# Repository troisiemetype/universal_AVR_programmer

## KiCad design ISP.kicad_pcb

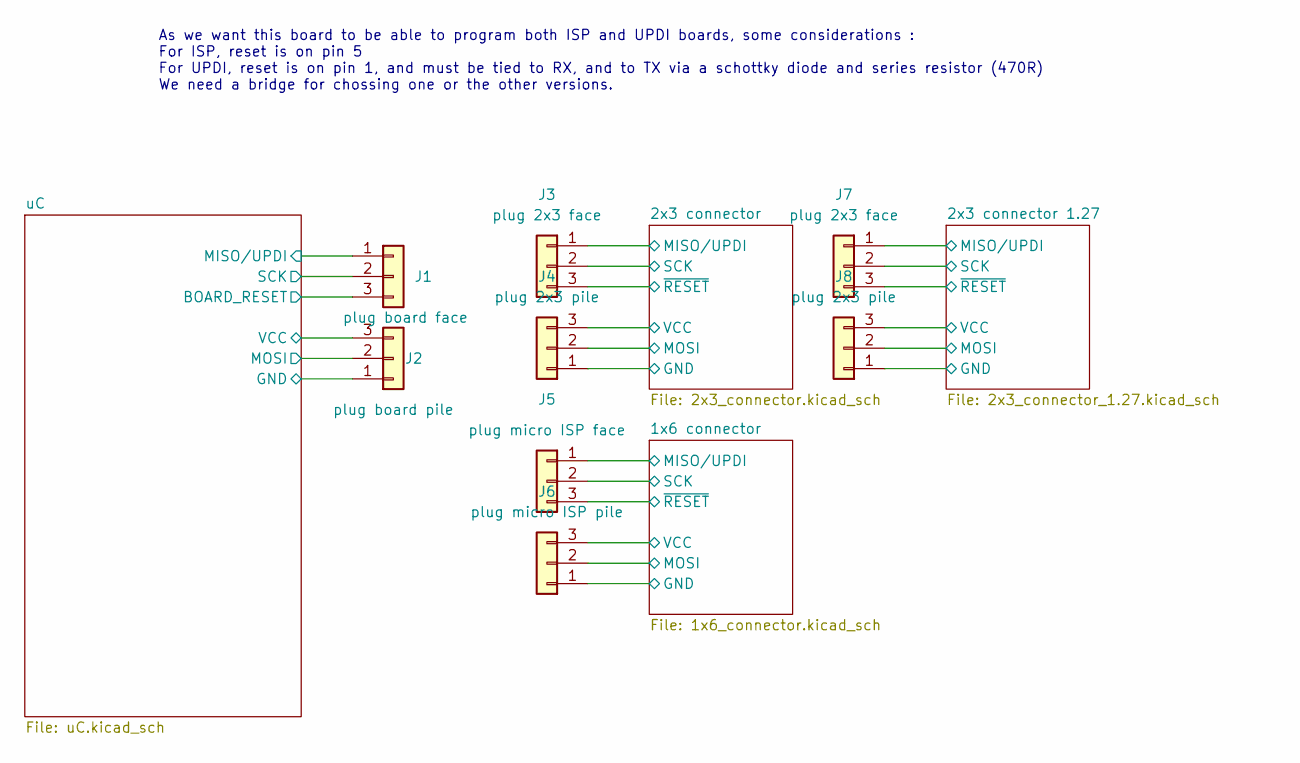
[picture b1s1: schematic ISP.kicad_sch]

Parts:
J1: plug board face; Connector_pad_1x03_P2.54mm
J2: plug board pile; Connector_pad_1x03_P2.54mm
J3, J7: plug 2x3 face; Connector_pad_1x03_P2.54mm
J4, J8: plug 2x3 pile; Connector_pad_1x03_P2.54mm
J5: plug micro ISP face; Connector_pad_1x03_P2.54mm
J6: plug micro ISP pile; Connector_pad_1x03_P2.54mm

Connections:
/1x6 connector/GND: J6.1; also elsewhere on the board
/1x6 connector/MISO/UPDI: J5.1; also elsewhere on the board
/1x6 connector/MOSI: J6.2; also elsewhere on the board
/1x6 connector/SCK: J5.2; also elsewhere on the board
/1x6 connector/VCC: J6.3; also elsewhere on the board
/1x6 connector/~RESET: J5.3; also elsewhere on the board
/2x3 connector 1.27/GND: J8.1; also elsewhere on the board
/2x3 connector 1.27/MISO/UPDI: J7.1; also elsewhere on the board
/2x3 connector 1.27/MOSI: J8.2; also elsewhere on the board
/2x3 connector 1.27/SCK: J7.2; also elsewhere on the board
/2x3 connector 1.27/VCC: J8.3; also elsewhere on the board
/2x3 connector 1.27/~RESET: J7.3; also elsewhere on the board
/2x3 connector/GND: J4.1; also elsewhere on the board
/2x3 connector/MISO/UPDI: J3.1; also elsewhere on the board
/2x3 connector/MOSI: J4.2; also elsewhere on the board
/2x3 connector/SCK: J3.2; also elsewhere on the board
/2x3 connector/VCC: J4.3; also elsewhere on the board
/2x3 connector/~RESET: J3.3; also elsewhere on the board
/uC/BOARD_RESET: J1.3; also elsewhere on the board
/uC/GND: J2.1; also elsewhere on the board
/uC/MISO/UPDI: J1.1; also elsewhere on the board
/uC/MOSI: J2.2; also elsewhere on the board
/uC/SCK: J1.2; also elsewhere on the board
/uC/VCC: J2.3; also elsewhere on the board

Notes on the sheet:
As we want this board to be able to program both ISP and UPDI boards, some considerations : For ISP, reset is on pin 5 For UPDI, reset is on pin 1, and must be tied to RX, and to TX via a schottky diode and series resistor (470R) We need a bridge for chossing one or the other versions.

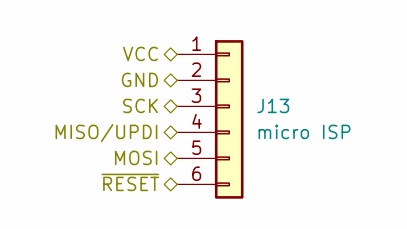
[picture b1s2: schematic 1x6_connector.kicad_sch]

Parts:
J13: micro ISP; Connector_pad_1x06_L10_P1.27mm

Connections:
/1x6 connector/GND: J13.2; also elsewhere on the board
/1x6 connector/MISO/UPDI: J13.4; also elsewhere on the board
/1x6 connector/MOSI: J13.5; also elsewhere on the board
/1x6 connector/SCK: J13.3; also elsewhere on the board
/1x6 connector/VCC: J13.1; also elsewhere on the board
/1x6 connector/~RESET: J13.6; also elsewhere on the board

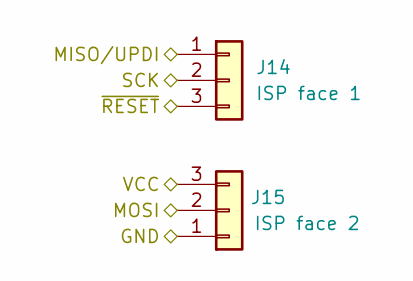
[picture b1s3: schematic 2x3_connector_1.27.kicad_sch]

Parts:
J14: ISP face 1; Connector_pad_1x03_L10_P1.27mm
J15: ISP face 2; Connector_pad_1x03_L10_P1.27mm

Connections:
/2x3 connector 1.27/GND: J15.1; also elsewhere on the board
/2x3 connector 1.27/MISO/UPDI: J14.1; also elsewhere on the board
/2x3 connector 1.27/MOSI: J15.2; also elsewhere on the board
/2x3 connector 1.27/SCK: J14.2; also elsewhere on the board
/2x3 connector 1.27/VCC: J15.3; also elsewhere on the board
/2x3 connector 1.27/~RESET: J14.3; also elsewhere on the board

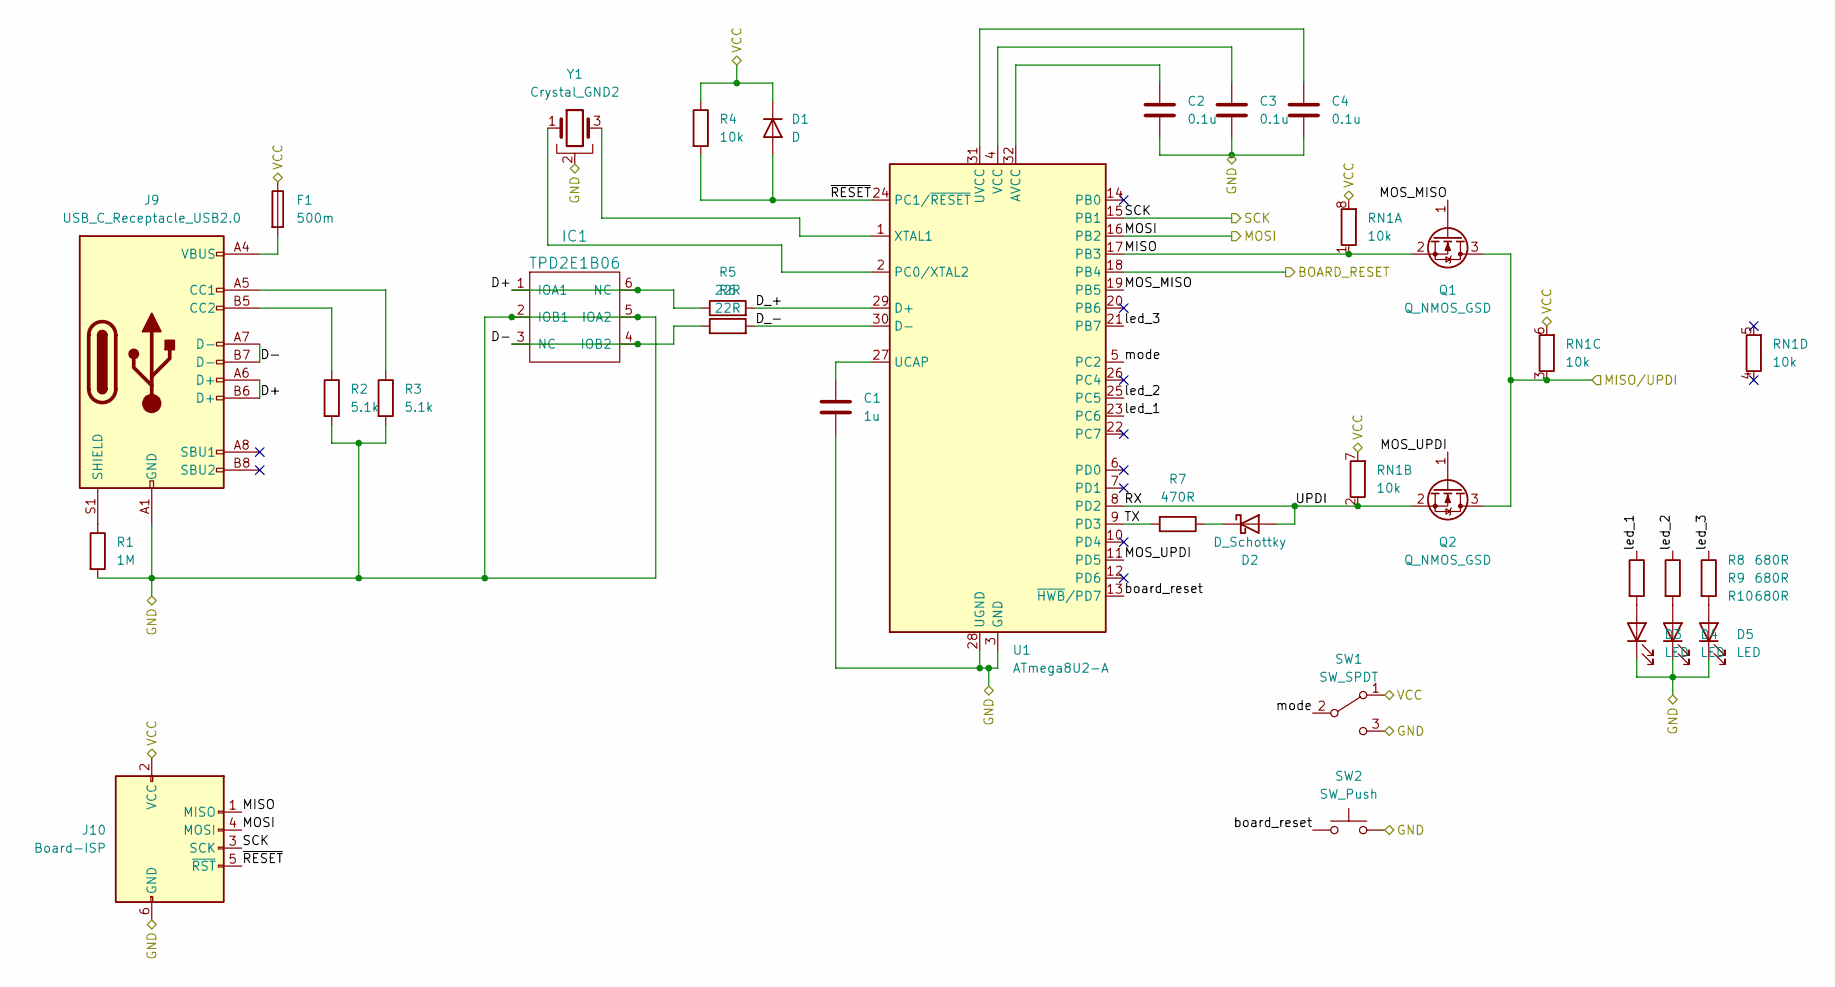
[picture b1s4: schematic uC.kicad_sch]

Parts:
C1: 1u; C_0603_1608Metric
C2, C3, C4: 0.1u; C_0603_1608Metric
D1: D; D_SOD-123
D2: D_Schottky; D_SOD-123
D3, D4, D5: LED; LED_0805_2012Metric
F1: 500m; Fuse_1206_3216Metric
IC1: TPD2E1B06; SOT-5X3
J9: USB_C_Receptacle_USB2.0; USB_C_Receptacle_GCT_USB4085
J10: Board-ISP; Pin_Header_Straight_2x03_Pitch2.54mm_SMD
Q1, Q2: Q_NMOS_GSD; SOT-23
R1: 1M; R_0603_1608Metric
R2, R3: 5.1k; R_0603_1608Metric
R4: 10k; R_0603_1608Metric
R5, R6: 22R; R_0603_1608Metric
R7: 470R; R_0603_1608Metric
R8, R9, R10: 680R; R_0603_1608Metric
RN1: 10k; R_Array_Convex_4x0603
SW1: SW_SPDT; SW_CuK_OS102011MA1QN1_SPDT_Angled
SW2: SW_Push; SW_SPST_EVPBF
U1: ATmega8U2-A; TQFP-32_7x7mm_P0.8mm
Y1: Crystal_GND2; Resonator_SMD_Murata_CSTxExxV-3Pin_3.0x1.1mm_HandSoldering

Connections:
/uC/BOARD_RESET: U1.18 (PB4); also elsewhere on the board
/uC/D+: IC1.1 (IOA1), IC1.6 (NC), J9.A6 (D+), J9.B6 (D+), R5.1
/uC/D-: IC1.3 (NC), IC1.4 (IOB2), J9.A7 (D-), J9.B7 (D-), R6.1
/uC/D_+: R5.2, U1.29 (D+)
/uC/D_-: R6.2, U1.30 (D-)
/uC/GND: C1.2, C2.2, C3.2, C4.2, D3.1 (K), D4.1 (K), D5.1 (K), IC1.2 (IOB1), IC1.5 (IOA2), J9.A1 (GND), J9.A12 (GND), J9.B1 (GND), J9.B12 (GND), J10.6 (GND), R1.2, R2.2, R3.2, SW1.3 (C), SW2.2, U1.3 (GND), U1.28 (UGND), Y1.2; also elsewhere on the board
/uC/MISO: J10.1 (MISO), Q1.2 (S), RN1.1 (R1.1), U1.17 (PB3)
/uC/MISO/UPDI: Q1.3 (D), Q2.3 (D), RN1.3 (R3.1); also elsewhere on the board
/uC/MOSI: J10.4 (MOSI), U1.16 (PB2); also elsewhere on the board
/uC/MOS_MISO: Q1.1 (G), U1.19 (PB5)
/uC/MOS_UPDI: Q2.1 (G), U1.11 (PD5)
/uC/RX: D2.2 (A), Q2.2 (S), RN1.2 (R2.1), U1.8 (PD2)
/uC/SCK: J10.3 (SCK), U1.15 (PB1); also elsewhere on the board
/uC/TX: R7.2, U1.9 (PD3)
/uC/VCC: D1.1 (K), F1.1, J10.2 (VCC), R4.1, RN1.6 (R3.2), RN1.7 (R2.2), RN1.8 (R1.2), SW1.1 (A); also elsewhere on the board
/uC/board_reset: SW2.1, U1.13 (~HWB/PD7)
/uC/led_1: R8.1, U1.23 (PC6)
/uC/led_2: R9.1, U1.25 (PC5)
/uC/led_3: R10.1, U1.21 (PB7)
/uC/mode: SW1.2 (B), U1.5 (PC2)
/uC/~RESET: D1.2 (A), J10.5 (~RST), R4.2, U1.24 (PC1/~RESET)
unnamed: C1.1, U1.27 (UCAP)
unnamed: C2.1, U1.32 (AVCC)
unnamed: C3.1, U1.4 (VCC)
unnamed: C4.1, U1.31 (UVCC)
unnamed: D2.1 (K), R7.1
unnamed: D3.2 (A), R8.2
unnamed: D4.2 (A), R9.2
unnamed: D5.2 (A), R10.2
unnamed: F1.2, J9.A4 (VBUS), J9.A9 (VBUS), J9.B4 (VBUS), J9.B9 (VBUS)
unnamed: J9.A5 (CC1), R3.1
unnamed: J9.B5 (CC2), R2.1
unnamed: J9.S1 (SHIELD), R1.1
unnamed: U1.1 (XTAL1), Y1.3
unnamed: U1.2 (PC0/XTAL2), Y1.1

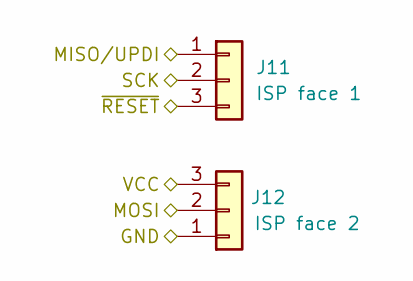
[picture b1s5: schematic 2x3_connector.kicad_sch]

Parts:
J11: ISP face 1; Connector_pad_1x03_L10_P2.54mm
J12: ISP face 2; Connector_pad_1x03_L10_P2.54mm

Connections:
/2x3 connector/GND: J12.1; also elsewhere on the board
/2x3 connector/MISO/UPDI: J11.1; also elsewhere on the board
/2x3 connector/MOSI: J12.2; also elsewhere on the board
/2x3 connector/SCK: J11.2; also elsewhere on the board
/2x3 connector/VCC: J12.3; also elsewhere on the board
/2x3 connector/~RESET: J11.3; also elsewhere on the board

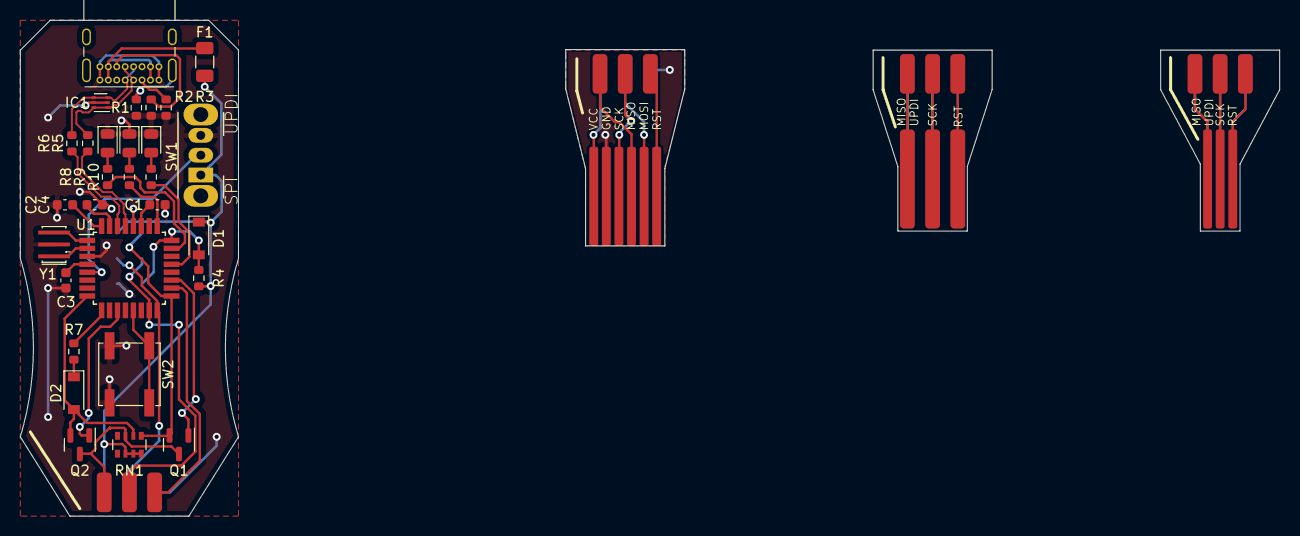
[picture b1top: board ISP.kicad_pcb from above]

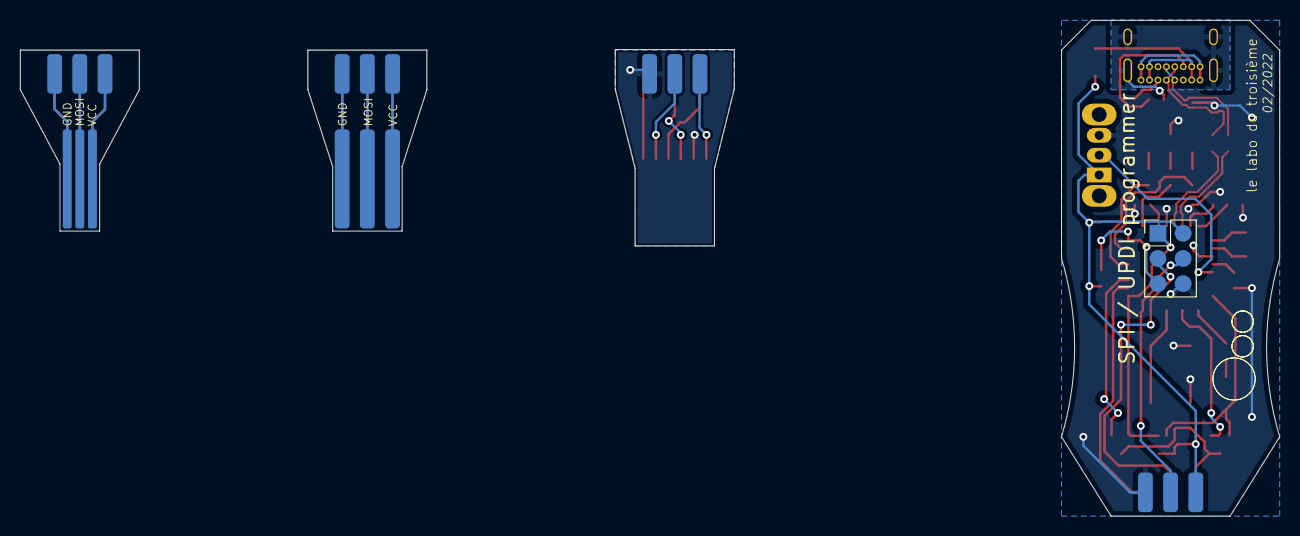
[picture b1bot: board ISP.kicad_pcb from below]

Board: 2 copper layers, 127.0 x 50.0 mm, 44 parts (8 on the bottom side), 53 nets.

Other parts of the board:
logo_labo_4mm: G***; logo_labo_4mm

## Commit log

2022-03-06 Initial commit. v1.0 sent to fab.
2022-03-29 Added components list. Added notes about modifications to be made on the next version. Added a beautiful example of how a board can be made to need bodging.
2022-03-29 Added schematics.
